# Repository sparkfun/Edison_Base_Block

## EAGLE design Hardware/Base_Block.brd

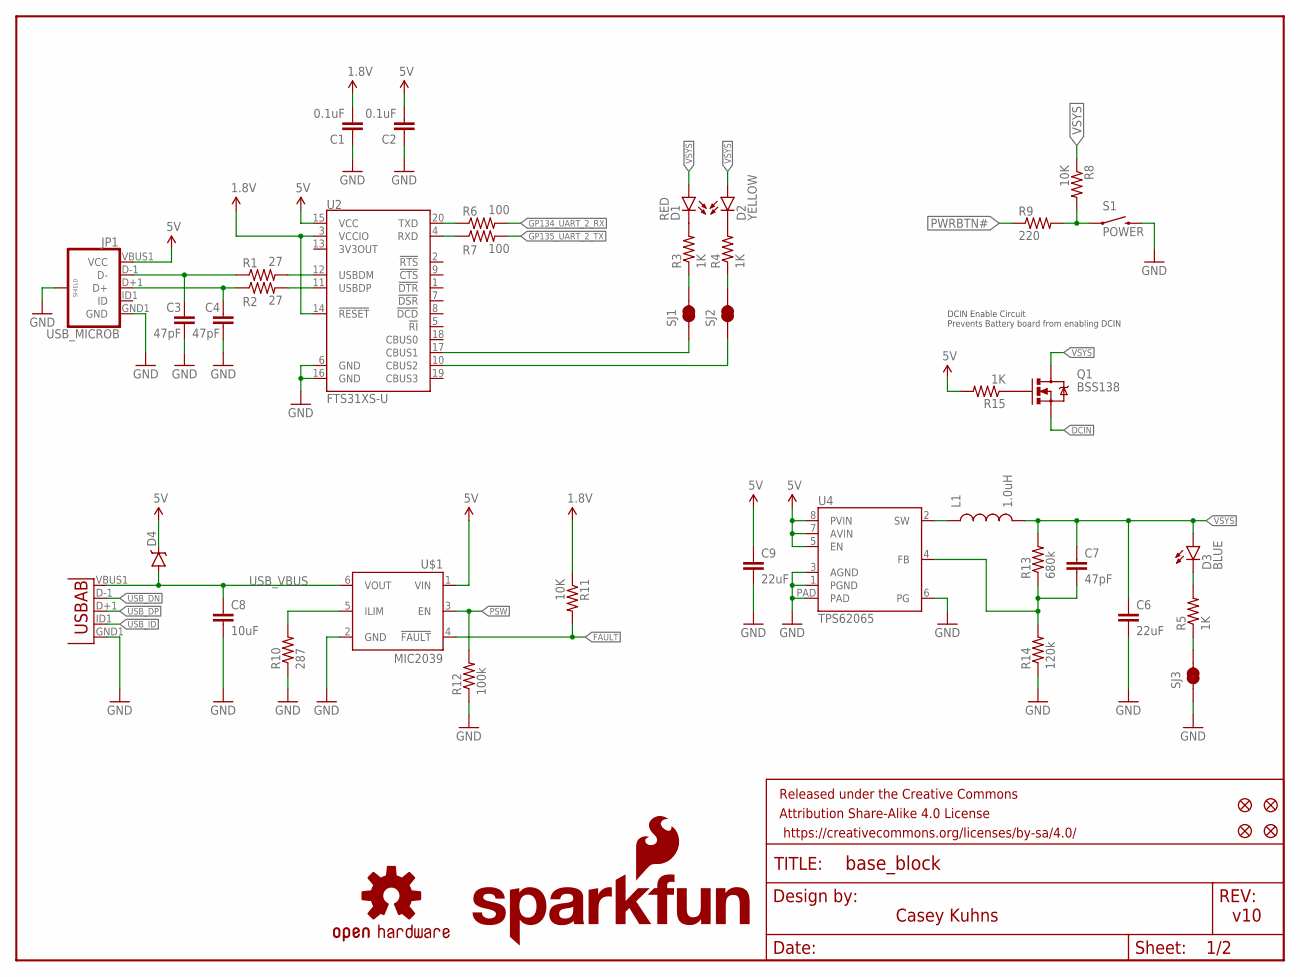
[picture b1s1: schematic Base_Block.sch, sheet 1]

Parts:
C1, C2: 0.1uF; 0603-CAP
C3, C4, C7: 47pF; 0603-CAP
C6, C9: 22uF; 0805
C8: 10uF; 1206
D1: RED; LED-0603
D2: YELLOW; LED-0603
D3: BLUE; LED-0603
D4: DIODE-SCHOTTKY-MBRA140; SMA-DIODE
FID1, FID2, FID3, FID4: FIDUCIAL1X2; FIDUCIAL-1X2
FRAME1: FRAME-LETTER; CREATIVE_COMMONS
JP1: USB_MICROB; USB-B-MICRO-SMD_V03
L1: 1.0uH; INDUCTOR-SRP4020
LOGO1: SFE_LOGO_NAME_FLAME.1_INCH; SFE_LOGO_NAME_FLAME_.1
LOGO4: OSHW-LOGOS; OSHW-LOGO-S
Q1: BSS138; SOT23-3
R1, R2: 27; 0603
R3, R4, R5, R15: 1K; 0603-RES
R6, R7: 100; 0603-RES
R8, R11: 10K; 0603-RES
R9: 220; 0603-RES
R10: 287; 0603-RES
R12: 100k; 0603-RES
R13: 680k; 0603-RES
R14: 120k; 0603-RES
S1: POWER; TACTILE_SWITCH-SMD-RIGHT-ANGLE
SJ1, SJ2, SJ3: JUMPER-PAD-2-NC_BY_TRACE; PAD-JUMPER-2-NC_BY_TRACE_YES_SILK
U2: FTS31XS-U; SSOP20_L
U3: USB-ABCONN-11794; USB-AB-MICRO-SMD_V03
U4: TPS62065; WSON-8-PAD
U$1: MIC2039; SOT23-6

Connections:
1.8V: C1.2, R11.1, U2.3 (VCCIO), U2.14 (!RESET); also elsewhere on the board
5V: C2.2, C9.1, D4.C, JP1.VBUS1 (VCC), R15.2, U2.15 (VCC), U4.5 (EN), U4.7 (AVIN), U4.8 (PVIN), U$1.1 (VIN)
DCIN: Q1.2 (S); also elsewhere on the board
FAULT: R11.2, U$1.4 (!FAULT); also elsewhere on the board
GND: C1.1, C2.1, C3.2, C4.2, C6.2, C8.2, C9.2, JP1.GND1 (GND), JP1.SHIELD1 (SHIELD), JP1.SHIELD2 (SHIELD), JP1.SHIELD3 (SHIELD), R10.1, R12.1, R14.1, S1.2, SJ3.1, U2.6 (GND), U2.16 (GND), U3.GND1 (GND), U4.1 (PGND), U4.3 (AGND), U4.6 (PG), U4.PAD, U$1.2 (GND); also elsewhere on the board
GP134_UART_2_RX: R6.2; also elsewhere on the board
GP135_UART_2_TX: R7.2; also elsewhere on the board
unnamed: SJ1.1, U2.17 (CBUS1)
unnamed: C3.1, JP1.D-1 (D-), R1.1
unnamed: C4.1, JP1.D+1 (D+), R2.1
unnamed: R1.2, U2.12 (USBDM)
unnamed: R2.2, U2.11 (USBDP)
unnamed: SJ2.1, U2.10 (CBUS2)
unnamed: R3.1, SJ1.2
unnamed: R4.1, SJ2.2
unnamed: D1.C, R3.2
unnamed: D2.C, R4.2
unnamed: R6.1, U2.20 (TXD)
unnamed: D3.C, R5.2
unnamed: R5.1, SJ3.2
unnamed: R7.1, U2.4 (RXD)
unnamed: R8.2, R9.2, S1.1
unnamed: R10.2, U$1.5 (ILIM)
unnamed: C7.2, R13.1, R14.2, U4.4 (FB)
unnamed: Q1.1 (G), R15.1
unnamed: L1.P$1 (1), U4.2 (SW)
PSW: R12.2, U$1.3 (EN); also elsewhere on the board
PWRBTN#: R9.1; also elsewhere on the board
USB_DN: U3.D-1 (D-); also elsewhere on the board
USB_DP: U3.D+1 (D+); also elsewhere on the board
USB_ID: U3.ID1 (USBID); also elsewhere on the board
USB_VBUS: C8.1, D4.A, U3.VBUS1 (VBUS), U$1.6 (VOUT); also elsewhere on the board
VSYS: C6.1, C7.1, D1.A, D2.A, D3.A, L1.P$2 (2), Q1.3 (D), R8.1, R13.2; also elsewhere on the board

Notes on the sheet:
DCIN Enable Circuit Prevents Battery board from enabling DCIN
Casey Kuhns
v10

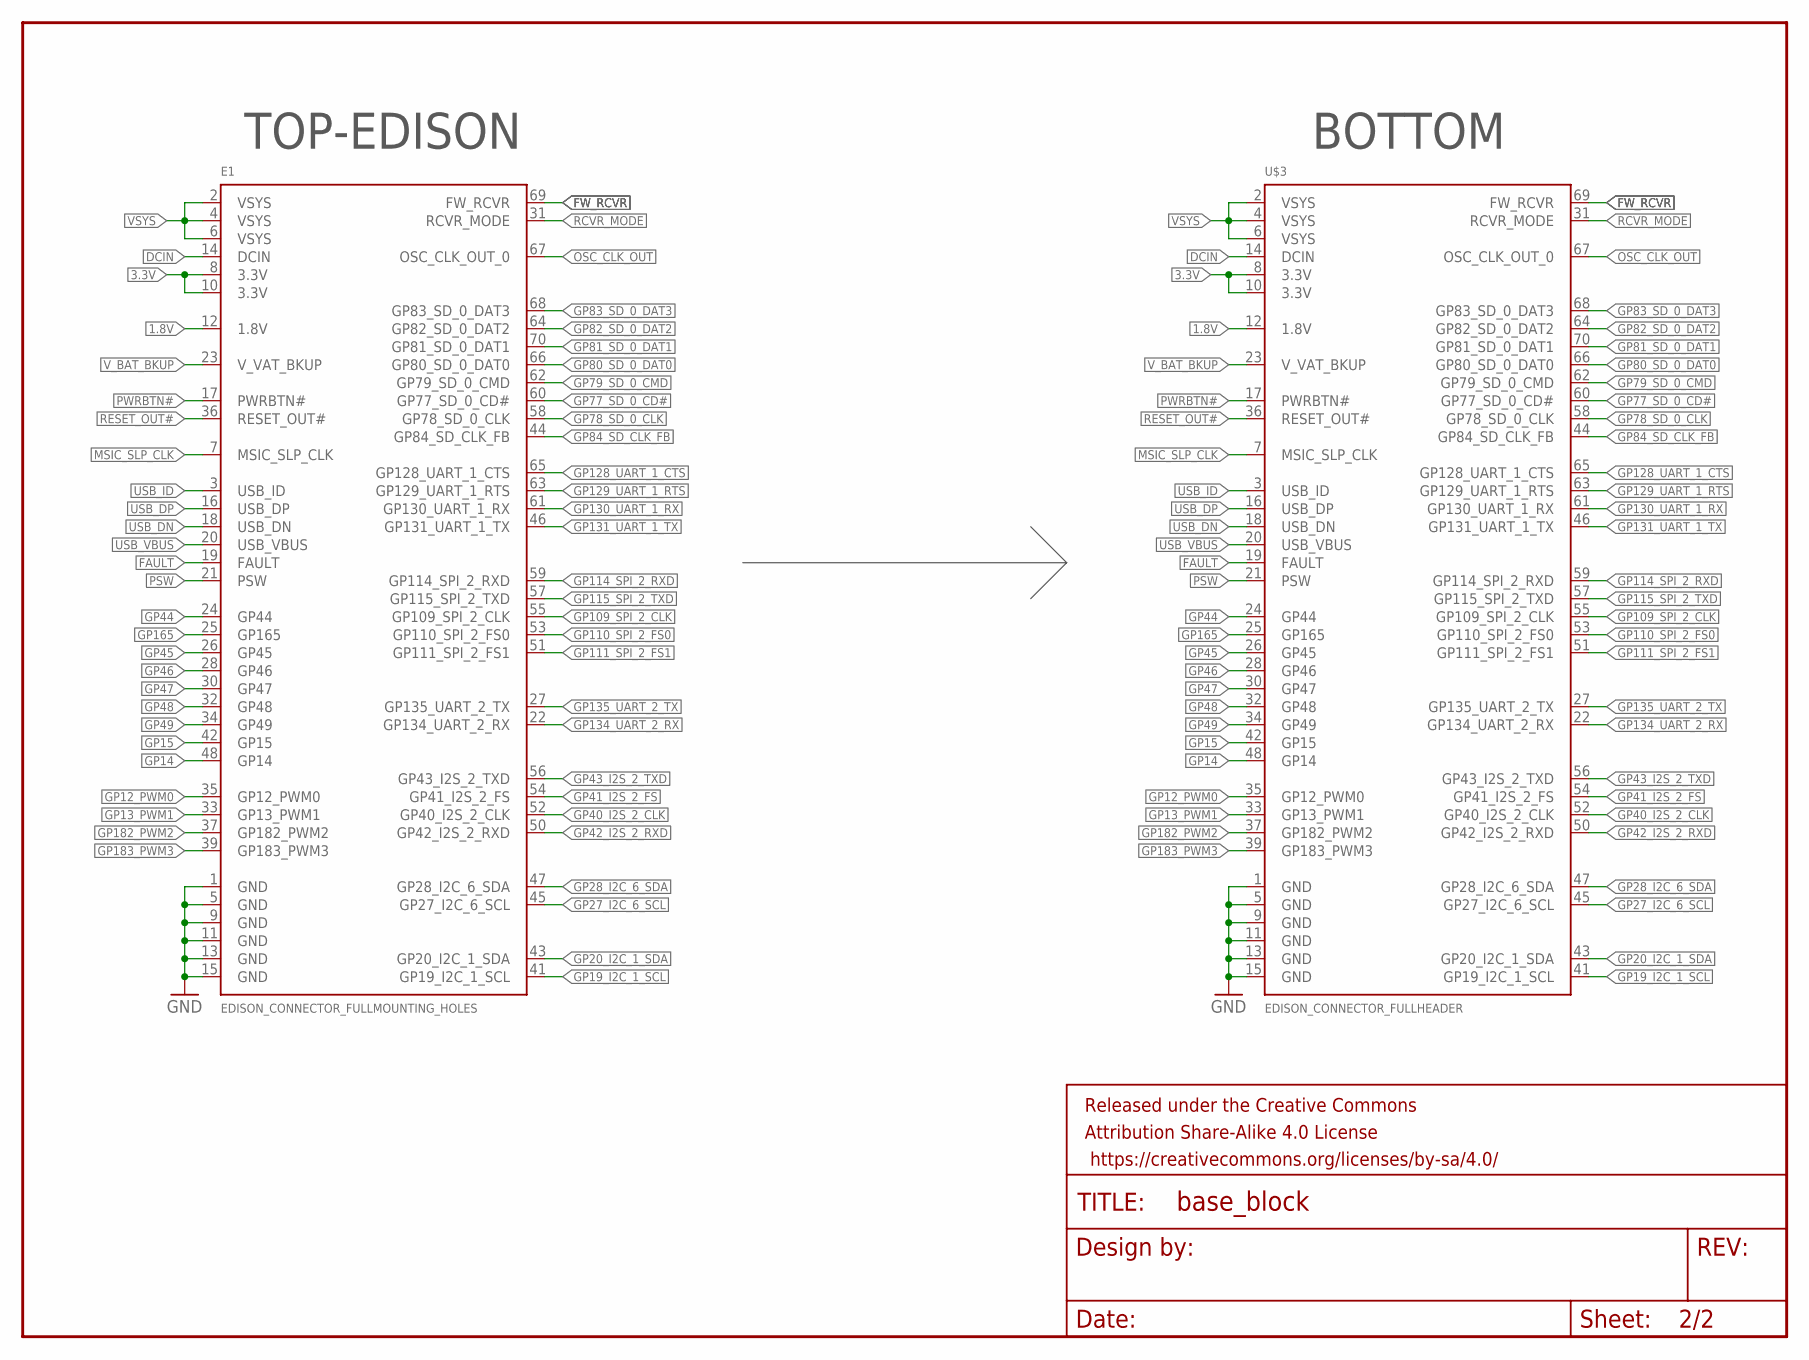
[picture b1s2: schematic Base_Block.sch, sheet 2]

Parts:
E1: EDISON_CONNECTOR_FULLMOUNTING_HOLES; EDISON_DAUGHTER
FRAME2: FRAME-LETTER; CREATIVE_COMMONS
U$3: EDISON_CONNECTOR_FULLHEADER; DF40C-70DP-0.4(51)

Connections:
1.8V: E1.12 (1.8V), U$3.12 (1.8V); also elsewhere on the board
3.3V: E1.8 (3.3V), E1.10 (3.3V), U$3.8 (3.3V), U$3.10 (3.3V)
DCIN: E1.14 (DCIN), U$3.14 (DCIN); also elsewhere on the board
FAULT: E1.19 (FAULT), U$3.19 (FAULT); also elsewhere on the board
FW_RCVR: E1.69 (FW_RCVR), U$3.69 (FW_RCVR)
GND: E1.1 (GND), E1.5 (GND), E1.9 (GND), E1.11 (GND), E1.13 (GND), E1.15 (GND), U$3.1 (GND), U$3.5 (GND), U$3.9 (GND), U$3.11 (GND), U$3.13 (GND), U$3.15 (GND); also elsewhere on the board
GP12_PWM0: E1.35 (GP12_PWM0), U$3.35 (GP12_PWM0)
GP13_PWM1: E1.33 (GP13_PWM1), U$3.33 (GP13_PWM1)
GP14: E1.48 (GP14), U$3.48 (GP14)
GP15: E1.42 (GP15), U$3.42 (GP15)
GP19_I2C_1_SCL: E1.41 (GP19_I2C_1_SCL), U$3.41 (GP19_I2C_1_SCL)
GP20_I2C_1_SDA: E1.43 (GP20_I2C_1_SDA), U$3.43 (GP20_I2C_1_SDA)
GP27_I2C_6_SCL: E1.45 (GP27_I2C_6_SCL), U$3.45 (GP27_I2C_6_SCL)
GP28_I2C_6_SDA: E1.47 (GP28_I2C_6_SDA), U$3.47 (GP28_I2C_6_SDA)
GP40_I2S_2_CLK: E1.52 (GP40_I2S_2_CLK), U$3.52 (GP40_I2S_2_CLK)
GP41_I2S_2_FS: E1.54 (GP41_I2S_2_FS), U$3.54 (GP41_I2S_2_FS)
GP42_I2S_2_RXD: E1.50 (GP42_I2S_2_RXD), U$3.50 (GP42_I2S_2_RXD)
GP43_I2S_2_TXD: E1.56 (GP43_I2S_2_TXD), U$3.56 (GP43_I2S_2_TXD)
GP44: E1.24 (GP44), U$3.24 (GP44)
GP45: E1.26 (GP45), U$3.26 (GP45)
GP46: E1.28 (GP46), U$3.28 (GP46)
GP47: E1.30 (GP47), U$3.30 (GP47)
GP48: E1.32 (GP48), U$3.32 (GP48)
GP49: E1.34 (GP49), U$3.34 (GP49)
GP77_SD_0_CD#: E1.60 (GP77_SD_0_CD#), U$3.60 (GP77_SD_0_CD#)
GP78_SD_0_CLK: E1.58 (GP78_SD_0_CLK), U$3.58 (GP78_SD_0_CLK)
GP79_SD_0_CMD: E1.62 (GP79_SD_0_CMD), U$3.62 (GP79_SD_0_CMD)
GP80_SD_0_DAT0: E1.66 (GP80_SD_0_DAT0), U$3.66 (GP80_SD_0_DAT0)
GP81_SD_0_DAT1: E1.70 (GP81_SD_0_DAT1), U$3.70 (GP81_SD_0_DAT1)
GP82_SD_0_DAT2: E1.64 (GP82_SD_0_DAT2), U$3.64 (GP82_SD_0_DAT2)
GP83_SD_0_DAT3: E1.68 (GP83_SD_0_DAT3), U$3.68 (GP83_SD_0_DAT3)
GP84_SD_CLK_FB: E1.44 (GP84_SD_CLK_FB), U$3.44 (GP84_SD_CLK_FB)
GP109_SPI_2_CLK: E1.55 (GP109_SPI_2_CLK), U$3.55 (GP109_SPI_2_CLK)
GP110_SPI_2_FS0: E1.53 (GP110_SPI_2_FS0), U$3.53 (GP110_SPI_2_FS0)
GP111_SPI_2_FS1: E1.51 (GP111_SPI_2_FS1), U$3.51 (GP111_SPI_2_FS1)
GP114_SPI_2_RXD: E1.59 (GP114_SPI_2_RXD), U$3.59 (GP114_SPI_2_RXD)
GP115_SPI_2_TXD: E1.57 (GP115_SPI_2_TXD), U$3.57 (GP115_SPI_2_TXD)
GP128_UART_1_CTS: E1.65 (GP128_UART_1_CTS), U$3.65 (GP128_UART_1_CTS)
GP129_UART_1_RTS: E1.63 (GP129_UART_1_RTS), U$3.63 (GP129_UART_1_RTS)
GP130_UART_1_RX: E1.61 (GP130_UART_1_RX), U$3.61 (GP130_UART_1_RX)
GP131_UART_1_TX: E1.46 (GP131_UART_1_TX), U$3.46 (GP131_UART_1_TX)
GP134_UART_2_RX: E1.22 (GP134_UART_2_RX), U$3.22 (GP134_UART_2_RX); also elsewhere on the board
GP135_UART_2_TX: E1.27 (GP135_UART_2_TX), U$3.27 (GP135_UART_2_TX); also elsewhere on the board
GP165: E1.25 (GP165), U$3.25 (GP165)
GP182_PWM2: E1.37 (GP182_PWM2), U$3.37 (GP182_PWM2)
GP183_PWM3: E1.39 (GP183_PWM3), U$3.39 (GP183_PWM3)
MSIC_SLP_CLK: E1.7 (MSIC_SLP_CLK), U$3.7 (MSIC_SLP_CLK)
OSC_CLK_OUT: E1.67 (OSC_CLK_OUT_0), U$3.67 (OSC_CLK_OUT_0)
PSW: E1.21 (PSW), U$3.21 (PSW); also elsewhere on the board
PWRBTN#: E1.17 (PWRBTN#), U$3.17 (PWRBTN#); also elsewhere on the board
RCVR_MODE: E1.31 (RCVR_MODE), U$3.31 (RCVR_MODE)
RESET_OUT#: E1.36 (RESET_OUT#), U$3.36 (RESET_OUT#)
USB_DN: E1.18 (USB_DN), U$3.18 (USB_DN); also elsewhere on the board
USB_DP: E1.16 (USB_DP), U$3.16 (USB_DP); also elsewhere on the board
USB_ID: E1.3 (USB_ID), U$3.3 (USB_ID); also elsewhere on the board
USB_VBUS: E1.20 (USB_VBUS), U$3.20 (USB_VBUS); also elsewhere on the board
VSYS: E1.2 (VSYS), E1.4 (VSYS), E1.6 (VSYS), U$3.2 (VSYS), U$3.4 (VSYS), U$3.6 (VSYS); also elsewhere on the board
V_BAT_BKUP: E1.23 (V_VAT_BKUP), U$3.23 (V_VAT_BKUP)

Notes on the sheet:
TOP-EDISON
BOTTOM

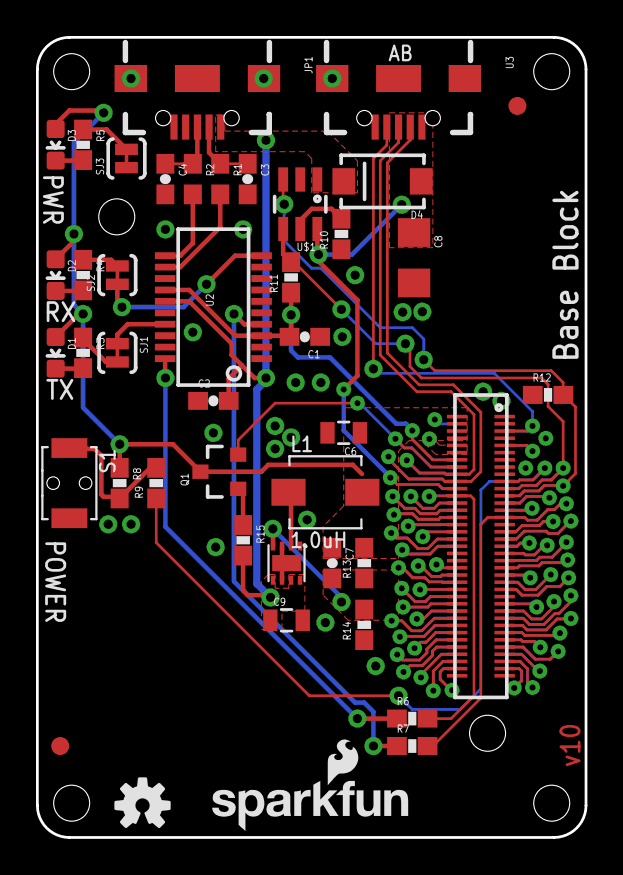
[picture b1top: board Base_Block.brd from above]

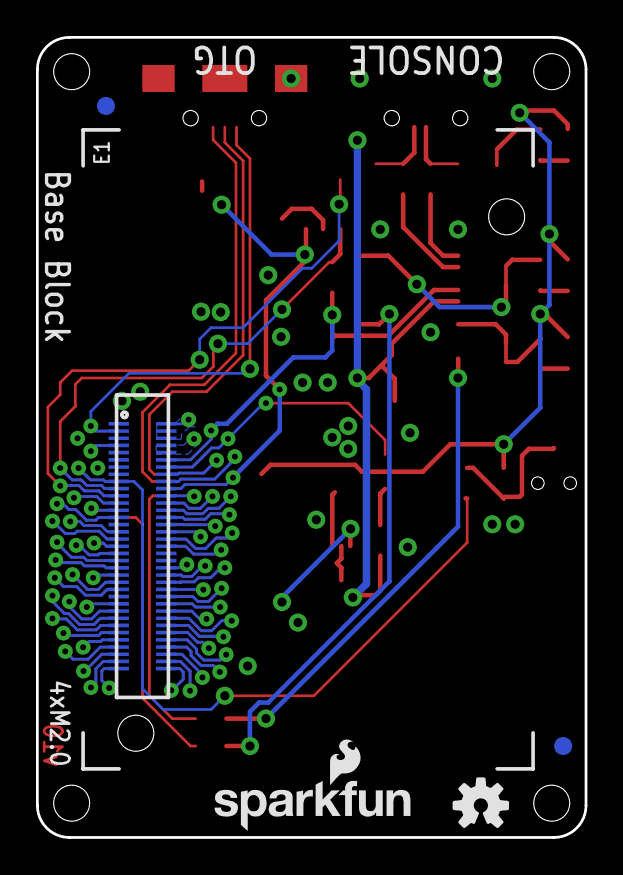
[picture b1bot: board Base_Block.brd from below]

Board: 2 copper layers, 30.5 x 44.5 mm, 50 parts (6 on the bottom side), 78 nets.

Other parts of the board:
LOGO2: OSHW-LOGOS; OSHW-LOGO-S
LOGO3: SFE_LOGO_NAME_FLAME.1_INCH; SFE_LOGO_NAME_FLAME_.1

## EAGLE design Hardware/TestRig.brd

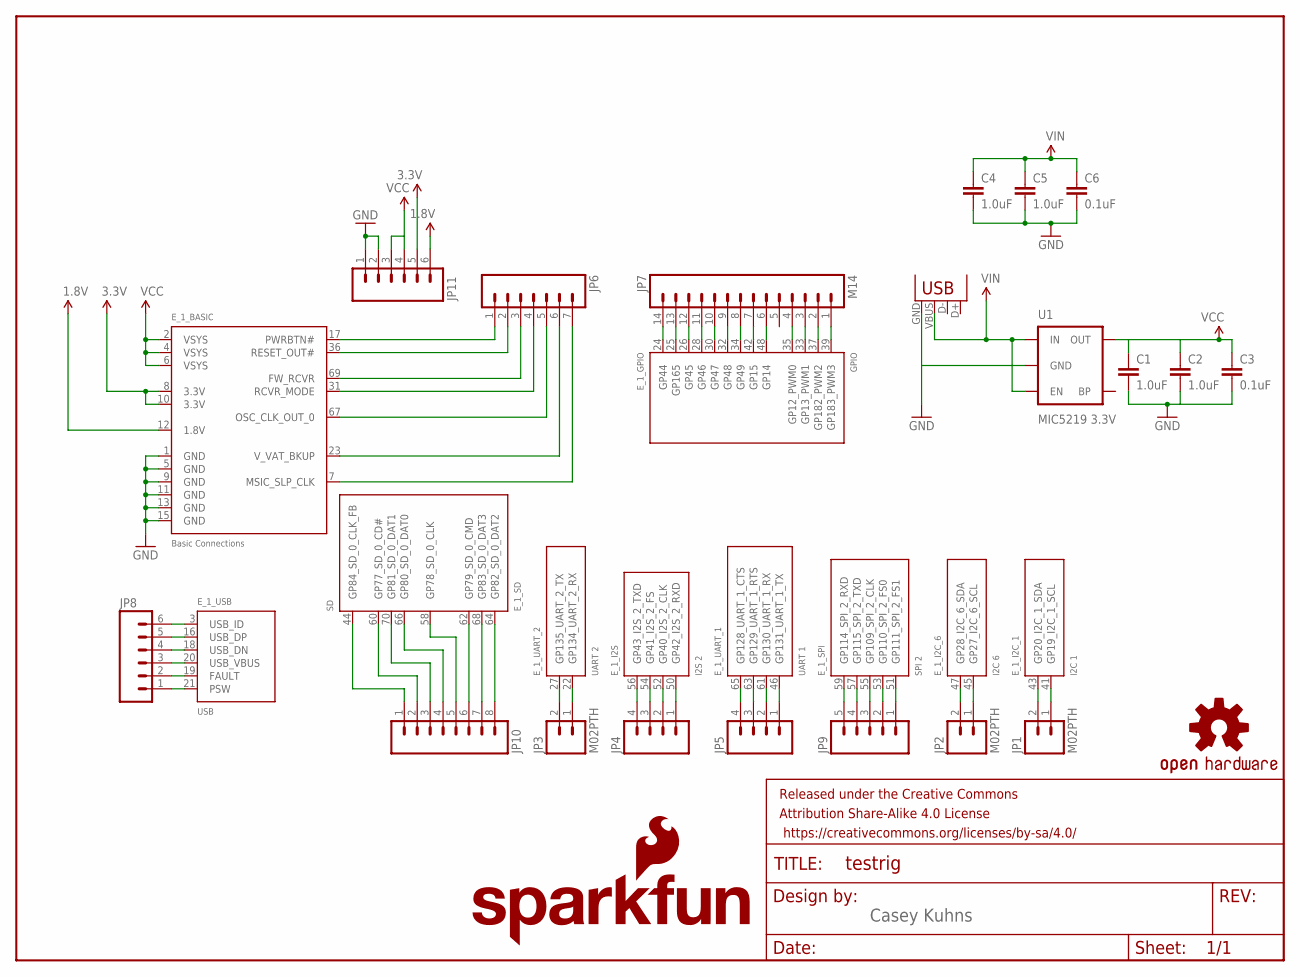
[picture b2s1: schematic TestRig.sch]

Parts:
C1, C2, C4, C5: 1.0uF; 0805
C3, C6: 0.1uF; 0603-CAP
E_1: EDISON_CONNECTOR_SEGMENTED; EDISON_DAUGHTER
FRAME1: FRAME-LETTER; CREATIVE_COMMONS
JP1, JP2, JP3: M02PTH; 1X02
JP4, JP5: M04PTH; 1X04
JP6: M07; 1X07
JP7: M14; 1X14
JP8, JP11: M06SIP; 1X06
JP9: M05NO_SILK; 1X05_NO_SILK
JP10: M081X08; 1X08
JP12: USBSMD; USB-MINIB
LOGO1: SFE_LOGO_NAME_FLAME.1_INCH; SFE_LOGO_NAME_FLAME_.1
LOGO2: OSHW-LOGOS; OSHW-LOGO-S
U1: MIC5219 3.3V; SOT23-5

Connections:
1.8V: E_1.12 (1.8V), JP11.6
3.3V: E_1.8 (3.3V), E_1.10 (3.3V), JP11.5
GND: C1.2, C2.2, C3.2, C4.2, C5.2, C6.2, E_1.1 (GND), E_1.5 (GND), E_1.9 (GND), E_1.11 (GND), E_1.13 (GND), E_1.15 (GND), JP11.1, JP11.2, JP12.GND, U1.2 (GND)
unnamed: E_1.41 (GP19_I2C_1_SCL), JP1.1
unnamed: E_1.43 (GP20_I2C_1_SDA), JP1.2
unnamed: E_1.45 (GP27_I2C_6_SCL), JP2.1
unnamed: E_1.47 (GP28_I2C_6_SDA), JP2.2
unnamed: E_1.22 (GP134_UART_2_RX), JP3.1
unnamed: E_1.27 (GP135_UART_2_TX), JP3.2
unnamed: E_1.50 (GP42_I2S_2_RXD), JP4.1
unnamed: E_1.52 (GP40_I2S_2_CLK), JP4.2
unnamed: E_1.54 (GP41_I2S_2_FS), JP4.3
unnamed: E_1.56 (GP43_I2S_2_TXD), JP4.4
unnamed: E_1.46 (GP131_UART_1_TX), JP5.1
unnamed: E_1.61 (GP130_UART_1_RX), JP5.2
unnamed: E_1.63 (GP129_UART_1_RTS), JP5.3
unnamed: E_1.65 (GP128_UART_1_CTS), JP5.4
unnamed: E_1.17 (PWRBTN#), JP6.1
unnamed: E_1.36 (RESET_OUT#), JP6.2
unnamed: E_1.69 (FW_RCVR), JP6.3
unnamed: E_1.31 (RCVR_MODE), JP6.4
unnamed: E_1.67 (OSC_CLK_OUT_0), JP6.5
unnamed: E_1.23 (V_VAT_BKUP), JP6.6
unnamed: E_1.7 (MSIC_SLP_CLK), JP6.7
unnamed: E_1.39 (GP183_PWM3), JP7.1
unnamed: E_1.37 (GP182_PWM2), JP7.2
unnamed: E_1.33 (GP13_PWM1), JP7.3
unnamed: E_1.35 (GP12_PWM0), JP7.4
unnamed: E_1.48 (GP14), JP7.6
unnamed: E_1.42 (GP15), JP7.7
unnamed: E_1.34 (GP49), JP7.8
unnamed: E_1.32 (GP48), JP7.9
unnamed: E_1.30 (GP47), JP7.10
unnamed: E_1.28 (GP46), JP7.11
unnamed: E_1.26 (GP45), JP7.12
unnamed: E_1.25 (GP165), JP7.13
unnamed: E_1.24 (GP44), JP7.14
unnamed: E_1.21 (PSW), JP8.1
unnamed: E_1.19 (FAULT), JP8.2
unnamed: E_1.20 (USB_VBUS), JP8.3
unnamed: E_1.18 (USB_DN), JP8.4
unnamed: E_1.16 (USB_DP), JP8.5
unnamed: E_1.3 (USB_ID), JP8.6
unnamed: E_1.51 (GP111_SPI_2_FS1), JP9.1
unnamed: E_1.53 (GP110_SPI_2_FS0), JP9.2
unnamed: E_1.55 (GP109_SPI_2_CLK), JP9.3
unnamed: E_1.57 (GP115_SPI_2_TXD), JP9.4
unnamed: E_1.59 (GP114_SPI_2_RXD), JP9.5
unnamed: E_1.64 (GP82_SD_0_DAT2), JP10.8
unnamed: E_1.68 (GP83_SD_0_DAT3), JP10.7
unnamed: E_1.62 (GP79_SD_0_CMD), JP10.6
unnamed: E_1.58 (GP78_SD_0_CLK), JP10.5
unnamed: E_1.66 (GP80_SD_0_DAT0), JP10.4
unnamed: E_1.70 (GP81_SD_0_DAT1), JP10.3
unnamed: E_1.60 (GP77_SD_0_CD#), JP10.2
unnamed: E_1.44 (GP84_SD_0_CLK_FB), JP10.1
VCC: C1.1, C2.1, C3.1, E_1.2 (VSYS), E_1.4 (VSYS), E_1.6 (VSYS), JP11.3, JP11.4, U1.5 (OUT)
VIN: C4.1, C5.1, C6.1, JP12.VBUS, U1.1 (IN), U1.3 (EN)

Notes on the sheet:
Casey Kuhns

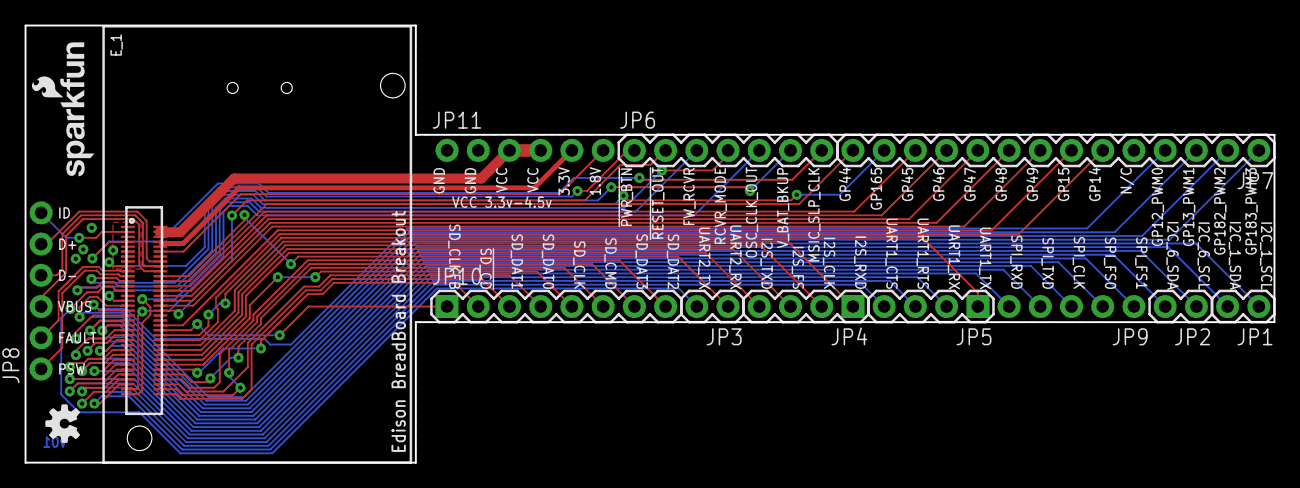
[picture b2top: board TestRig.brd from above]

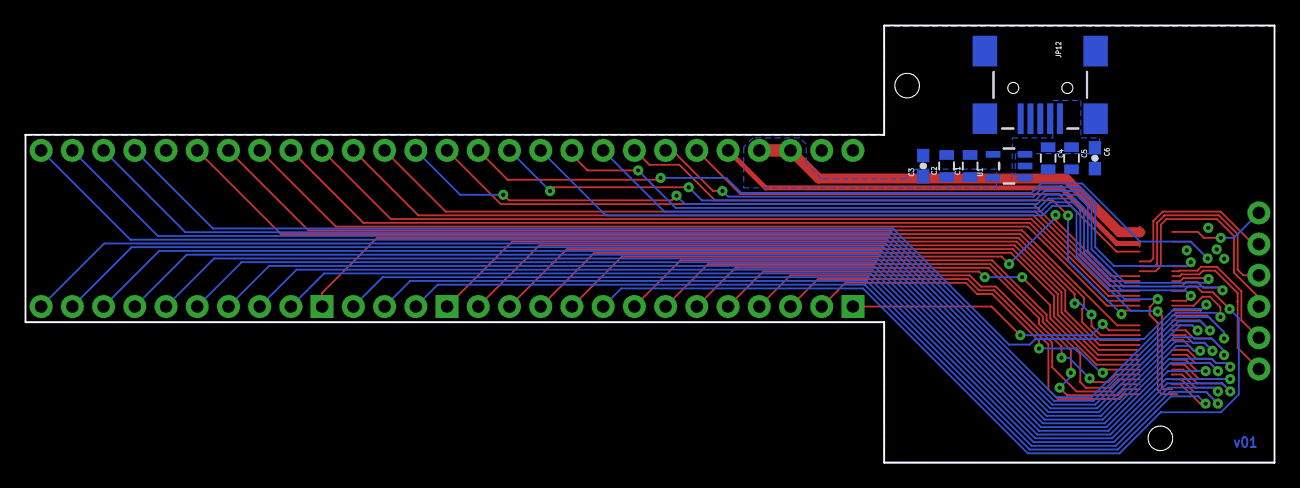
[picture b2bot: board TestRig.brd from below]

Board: 2 copper layers, 101.6 x 35.6 mm, 23 parts (8 on the bottom side), 58 nets.

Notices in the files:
parts and their libraries:
SparkFun-Aesthetics: Licensing: Creative Commons ShareAlike 4.0 International - https://creativecommons.org/licenses/by-sa/4.0
SparkFun-Aesthetics: Released under the Creative Commons Attribution Share-Alike 4.0 License
SparkFun-Aesthetics: https://creativecommons.org/licenses/by-sa/4.0
